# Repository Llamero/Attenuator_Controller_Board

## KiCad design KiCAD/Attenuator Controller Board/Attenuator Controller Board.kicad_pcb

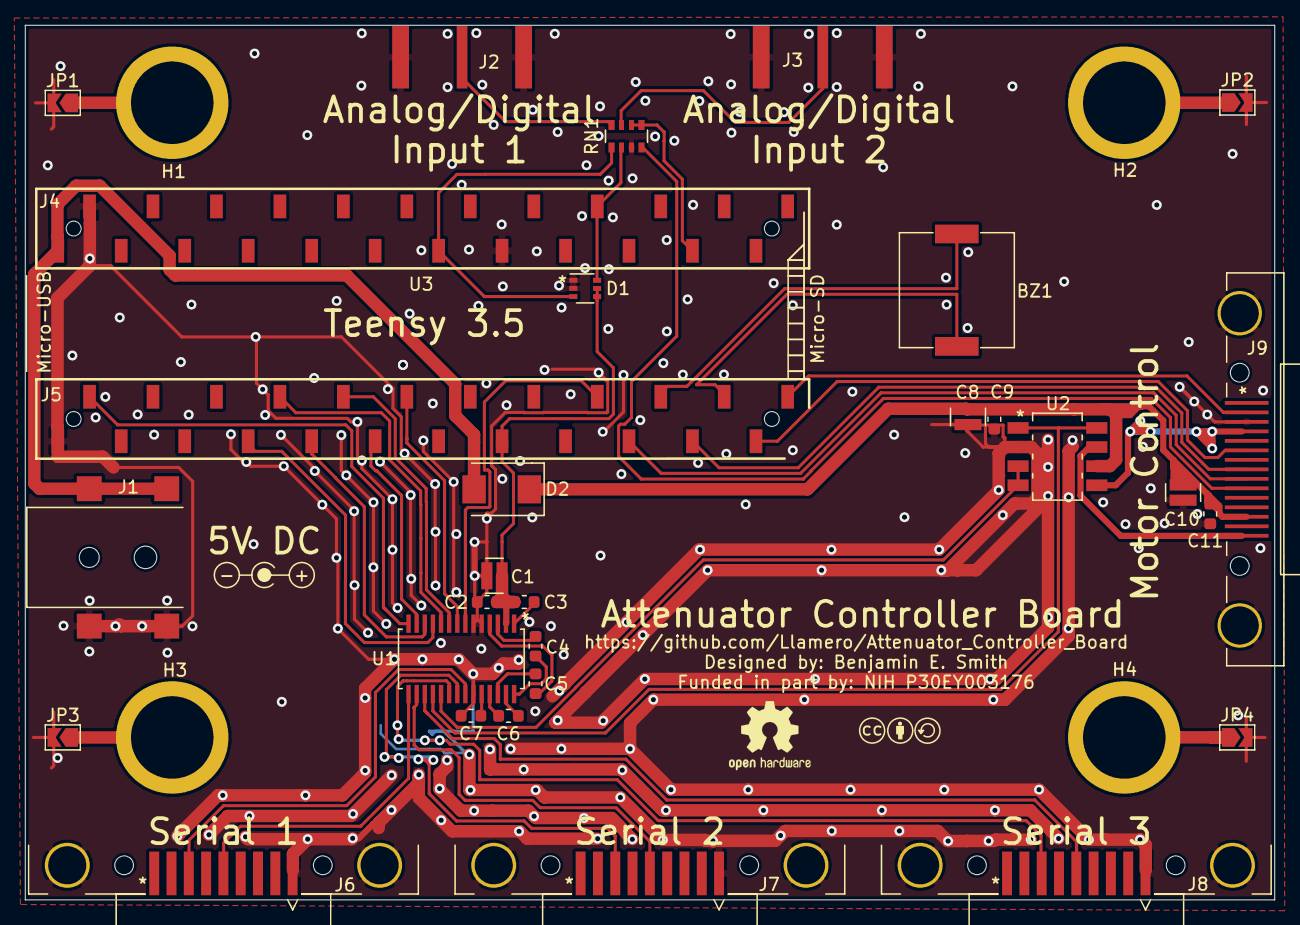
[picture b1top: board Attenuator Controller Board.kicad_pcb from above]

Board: 2 copper layers, 100.0 x 70.0 mm, 38 parts (0 on the bottom side), 46 nets.

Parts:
BZ1: CPT-2016-75-SMT-TR; SMT-0940-T-3V-R_9x9_alarm
C1, C8, C10: 10µF; 0508_Capacitor
C2, C3, C4, C5, C6, C7, C9, C11: 0.1µF; C_0603_1608Metric
D1: BAT54BRW; SOT-363_SC-70-6
D2: D_Schottky; DO-214BA
H1, H2, H3, H4: MountingHole; 1_4-20_Clearance_hole
J1: Barrel_Jack_Switch; DC-jack_54-00165
J2, J3: Conn_Coaxial; 112640
J4, J5: Conn_01x24_Female; Ref_only
J6, J7, J8: DSub9; K202XHT-E9P-N
J9: DSub_15_HD; 200-015-263R001
JP1, JP2, JP3, JP4: Jumper_NC_Small; SolderJumper-2_P1.3mm_Open_TrianglePad1.0x1.5mm
LOGO1: CC license; Creative_commons_license
LOGO2: Jack Polarity; Polarity_Center_Positive
LOGO3: OSHW Logo; OSHW-Logo2_7.3x6mm_SilkScreen
RN1: 4.7k; R_Array_Convex_4x0603
U1: ADM3307EARUZ
U2: ZXMHC3A01T8TA
U3: Teensy3.5; Teensy_3_6_with_headers

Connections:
/3v3: C1.1, C2.1, C3.2, D1.4, D1.5, U1.2, U3.15
/5V: D2.2, J1.1, U3.53
/Alarm1: BZ1.1, U3.22
/Alarm2: BZ1.2, U3.20
/Analog_Input1: D1.3, RN1.1, U3.41
/Analog_Input2: D1.6, RN1.2, U3.36
/Encoder(A): J9.11, U3.24
/Encoder(B): J9.13, U3.21
/Forward_Limit_Switch: J9.2, U3.23
/Gate1-2: U1.19, U2.3, U2.4
/Gate3-4: U1.18, U2.1, U2.8
/Ident(-): RN1.5, RN1.6, U3.33
/Ident_In: J9.9, RN1.4
/Motor1: U1.10, U3.8
/Motor2: U1.11, U3.7
/Motor(+): J9.7, U2.5
/Motor(-): J9.5, U2.7
/RS-232_RXD1: J6.3, U1.15
/RS-232_RXD2: J7.3, U1.16
/RS-232_RXD3: J8.3, U1.17
/RS-232_TXD1: J6.2, U1.22
/RS-232_TXD2: J7.2, U1.21
/RS-232_TXD3: J8.2, U1.20
/Reverse_Limit_Switch: J9.3, U3.19
/Serial1-RX: U1.14, U3.2
/Serial1-TX: U1.7, U3.18
/Serial2-RX: U1.13, U3.11
/Serial2-TX: U1.8, U3.12
/Serial3-RX: U1.12, U3.9
/Serial3-TX: U1.9, U3.10
GND: C1.2, C2.2, C7.2, C8.2, C9.1, C10.2, C11.1, D1.1, D1.2, J1.2, J1.3, J2.2, J3.2, J6.5, J6.10, J7.5, J7.10, J8.5, J8.10, J9.1, J9.16, JP1.2, JP2.2, JP3.2, JP4.2, RN1.3, U1.5, U1.6, U1.23, U2.2, U3.1, U3.39, U3.52
unnamed: C3.1, U1.1
unnamed: C4.1, U1.28
unnamed: C4.2, U1.3
unnamed: C5.1, U1.26
unnamed: C5.2, U1.4
unnamed: C6.1, U1.27
unnamed: C6.2, U1.25
unnamed: C7.1, U1.24
unnamed: C8.1, C9.2, C10.1, C11.2, D2.1, J9.10, U2.6
unnamed: H1.1, JP1.1
unnamed: H2.1, JP2.1
unnamed: H3.1, JP3.1
unnamed: H4.1, JP4.1
unnamed: J2.1, RN1.8
unnamed: J3.1, RN1.7

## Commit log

2022-01-11 Rebuild schematic- git can be frustrating sometimes
2022-01-11 BNC clamps and alarm added
2022-01-11 Initial PCB layout
2022-01-11 Schottky diode protecting Vin->motor added
2022-01-11 Started on traces
2022-01-12 RS-232 outs connected and shielded
2022-01-12 Keep SD and EN low to keep RS-232 driver always on
2022-01-12 Disconnect SD and EN from Teensy
2022-01-12 Started on Thorlabs connections
2022-01-13 More DSub-15 connections
2022-01-13 DSub 9 aligned
2022-01-13 Complete draft - all connected - need to double check pinouts
2022-01-14 Motor pinout now matches K-cube specification
    https://www.thorlabs.com/newgrouppage9.cfm?objectgroup_id=2419
2022-01-14 Cleaned up traces
2022-01-18 Re-order annotation - add 0.1µF bypass to bypass H-bridge
2022-01-18 Ground connector housing and standoffs
2022-01-18 Optional grounding of standoffs - ordered revision
2022-01-18 Split controls in GUI
2022-01-19 Main display draft complete
2022-02-04 Fixed RN footprint - Test draft of Teensy code
2022-02-10 GUI draft
2022-02-11 labelling main gui panel
2022-03-07 Minimal Arduino code
2022-03-07 home offset is not in degrees
2022-03-08 Add configure pins to functions stops motor from freezing
2023-01-12 Update GUI

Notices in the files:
parts and their libraries:
Copyright 2021 Accelerated Designs. All rights reserved.
